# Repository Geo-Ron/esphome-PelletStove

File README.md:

# esphome-PelletStove

This repository is dedicated to documenting the maintenance, parts, communication and controls of the pellet stove my mother bought recently (september 2024).

I am going to be a parasite and feed on the work of someone else: https://github.com/jazzmonger/wood-pellet-stove-with-TYWE1S-Tuya-chip. Read his [discussions section](https://github.com/jazzmonger/wood-pellet-stove-with-TYWE1S-Tuya-chip/discussions), they are AWESOME! Many, many, many thanks in advanced.

## The story

<details>
  <summary>In short: the gas fireplace was replaced with a used pellet stove.</summary>
  
My mother (80+) and father (70+) were really happy with their gas stove.

They enjoyed the warmth and liked turning the heat up to more then 22°C, as most elderly people do.

I remember I always had a hard time staying awake in these temperatures in winter times.

But then the war in Ukrain broke loose and gas prices went up in the Netherlands. My parents were shocked by the news reports about the high gas prices and decided to stop turning on the gas fireplace to lower their monthly costs.

In basis that was a really good decision, if it were not for the fact that their 1960's house was not that nicely isolated.

Their next decision was to stop heating around 18h and heat only the living room with an electric heater up to 19°C. My mother also bought a cordless electric heating cushion for her back.

It was kind of okay for them, with some amount of complaining by my mother. She wore several layers of clothing and still was not comfortable.

I then decided to look for an alternative for their unused gas fireplace, but was limited by the fact that they absolutely did not want to invest thousands of Euros in a new fireplace. As they stated: they were too old for such an investment.

So the search was for a used pellet stove, that would fit the hole in the wall.

It took me more then a year to find one with an acceptable price. My father passed away during my search, so he was not going to benefit from it anymore.

Then I found one, the price was okay. The seller did not know of a manufacturer or model number. The gamble was on me to risk the money of someone else. 

The seller was nice and told us he had a good history with this stove. The reason for him to sell it was that it was getting too hot in his home. In my opinion that was not going to be an issue at my mothers place.

The device was demo-ed and we took it home.

</details>

## The 'new' pellet stove

<details>
<summary>
We bought a HY IN9A. Probably this is a rebranded device sold by the company 'Justfire' in the Netherlands. The original manufacturer is [HYStove](https://hystove.en.alibaba.com/)
</summary>

When Google-ing the model name, this led us to the site [http://histove.com](http://histove.com/?AirPelletStove/51.html). The manufacturing company (I assume) is HAINING HEYING HEATING TECHNOLOGY CO., LTD.

At this moment sold at [Alibaba.com](https://www.alibaba.com/product-detail/House-heating-use-modern-eco-friendly_62325821470.html)

### Site Model information

Model: **HY-IN9A**

Capacity: _9KW_

Description: 2019 newly designed European style insert wood pellet stove

| Product parameters(HY-IN9A) |                 |
|-----------------------------|-----------------|
| Heat Area                   | 100㎡            |
| Dimension(W\*H\*D)          | 807\*635\*621mm |
| Air input pipe              | 50mm            |
| Air outlet pipe             | 80mm            |
| Auto-burning Time           | 13h-27h         |
| Consumption for pellet      | 0.8-1.8kg/h     |
| Efficiency                  | 90%             |
| Hopper Capacity             | 23kg            |
| Electronic comsuotion       | 100-400W/h      |
| Rating voltage              | 230v            |

Specifications:

1. Outside: steel coating.
2. Inside: monobloc steel structure, hand welded, heat-resistant up to 1200°C.
3. Door: carbon steel, high temperature resistant, with glass-ceramic.
4. Removable ash box: it collects the ash fallen through the holes in the brazier.
5. Glass-self cleaning: designing wind to blow ash from the glass keeps the glass always cleaning.
6. LCD control panel: it is placed on the upper side of the stove, simple and easy to be used. It is possible to plan the weekly switching on and off of the stove (week-end included).
7. Thermostat: The stove can keep the room's temperature stably. The temperature can be selected by users both on the panel and remote control, showing on the display.
8. Five steps power setting: it is up to your need, which also shows on the display.
9. Remote control
10. Smoke outlet: ø 80 mm, inlet ø 50 mm
11. Electrical supply: 230V-50Hz. 115V-60HZ, 100V-50HZ

### Not entirely true

As one can read, the information provided is mostly correct. So that is a starting point.

### Image search

So I tried to image search the stove I bought and there were several options:

- It is sold as a [Justfire PS-15-5 BUILDIN](https://justfire.nl/pellethaard-9kw-standard-type-black-2500.html)
- It is a Nemaxx stove (once sold in Germany)
  - The Nemaxx P6 is **identical** to the HY 6A.
- Cleveland Ironworks stove.
  - Their model [No.215](https://www.cleveland-ironworks.com/no-215-mini-pellet-stove.html) really looks like the same HY 6A.
- But also other brands: Sole, Grace Ningbo

</details>

## First basic maintenance

<details>
<summary>
Getting spare parts is not 'cheap'
</summary>

I am by no means a pellet stove expert. Let me get this out first.

What I am is a technical person. Problem solving is my job and I really like making things simple.

So I used my ash-vacuum-cleaner and take a deeper look into it.

The stove was almost clean, with some sealings ruptured.

Then I asked the company Justfire for a maintenance quote, and their response was this:

- Incidental maintenance: €300,-
- the mainboard (MCU) would need replacement because of a fire hazard: €200,-
- the display would need to match the MCU and would also be replaced: €170,-
- the ruptured seals would probably be included in the maintenance, if not that would add another €80,-

**No way that I am going to pay €750,-** for a first maintenance and inspection. They did not ask me for any serial number, model number, date of manufacturing or anything else.

I investigated other sellers for just the sealing-replacements than Justfire, but was unable to find all the seals that I needed. So I paid €80,- for two sealings at Justfire. These I can replace myself easily.

Half an hours of vacuuming, brushing and replacing the seals and we are in business for now.

</details>

### Spare parts

I will list all the parts I buy and/or replace in [parts-list.md](./parts-list.md).

### The missing remote

<details>
<summary>Unable to find a replacement remote control
</summary>

I found out the stove should have a remote. This would be nice so my mother would not need to bend over to control the stove.

I was unable to find a replacement remote for a price less then €80,-. That is too much as far as I am concerned. No guarantees that the remote would work anyway.

Justfire also sells a WiFi module for the ginormous amount of €160,-. But for an extra €160,- they are willing to configure it for me 😄.

</details>

### And then I found the jazzmonger github repository

When I found the [Github repository of Jazzmonger](https://github.com/jazzmonger/wood-pellet-stove-with-TYWE1S-Tuya-chip) I was overwhelmed with his work and enthousiasm. Wow!

I already have an [HomeAssistant](https://www.home-assistant.io/) instance at my mothers house, to monitor gas usage and room temperatures. It would really be a nice addition to connect the stove to it.

What I would really like to accomplish is:

- Be able to remotely control the stove from HomeAssistant
  - Turn it on/off
  - change the ECO mode
  - change the P1-4 modes
  - be able to measure temperatures
  - reading the stove 'states'
  - detect and reset errors
  - monitor the pellet level
- All without any 'special' PCBs to buy
  - I mean, I have several ESP32's laying around and I am willing to assemble a PCB of some sort and order material.

But most, if not all, of the heavy lifting has been done by [Jazzmonger](https://github.com/jazzmonger) already.

What I need to do is:

- Understand what he has accomplished, how it works and how to copy/adapt/improve his work.
  - I will be returning to him as I improve. Promised.

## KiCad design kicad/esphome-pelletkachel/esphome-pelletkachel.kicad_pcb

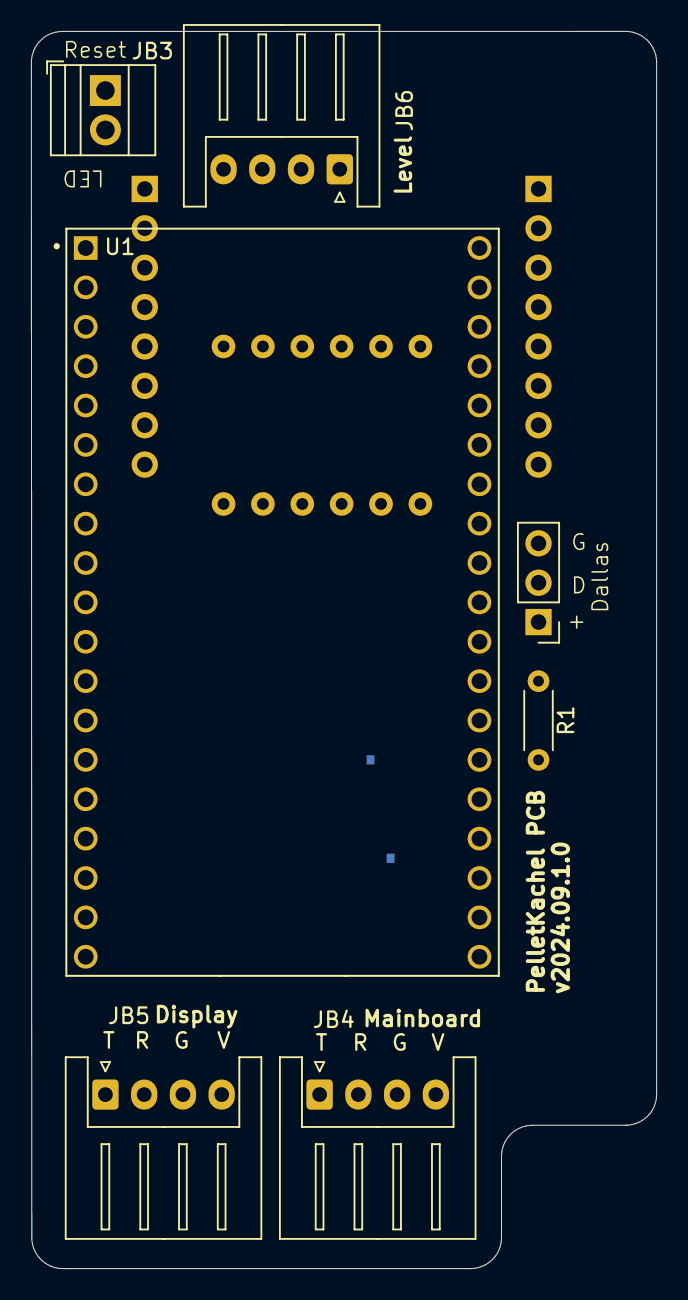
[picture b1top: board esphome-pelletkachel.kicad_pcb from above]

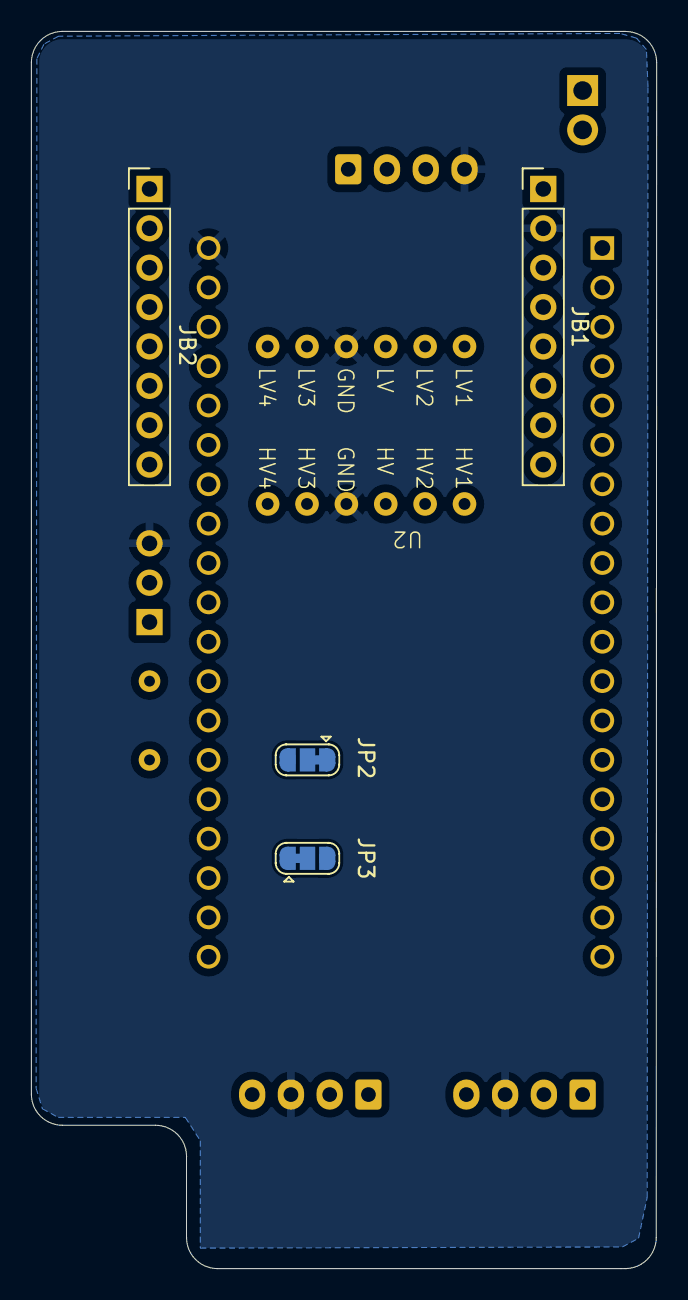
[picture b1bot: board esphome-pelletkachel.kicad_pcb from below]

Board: 2 copper layers, 40.3 x 79.8 mm, 12 parts (5 on the bottom side), 19 nets, no tracks yet.

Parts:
J6: 1-wire; PinHeader_1x03_P2.54mm_Vertical
JB1: J5 Even; PinHeader_1x08_P2.54mm_Vertical
JB2: J5 Odd; PinHeader_1x08_P2.54mm_Vertical
JB3: Thumbs; TerminalBlock_Xinya_XY308-2.54-2P_1x02_P2.54mm_Horizontal
JB4: Mainboard (DPC); JST_XH_S4B-XH-A_1x04_P2.50mm_Horizontal
JB5: Display (J1); JST_XH_S4B-XH-A_1x04_P2.50mm_Horizontal
JB6: To TOF; JST_XH_S4B-XH-A_1x04_P2.50mm_Horizontal
JP2: RX switcher; SolderJumper-3_P1.3mm_Bridged12_RoundedPad1.0x1.5mm
JP3: TX switcher; SolderJumper-3_P1.3mm_Bridged12_RoundedPad1.0x1.5mm
R1: 1k; R_Axial_DIN0204_L3.6mm_D1.6mm_P5.08mm_Horizontal
U1: ESP32-DEVKITC-32U; MODULE_ESP32-DEVKITC-32U
U2: 757; TT-4chLLC-SKU000275

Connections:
+3.3V: J6.1, JB6.1, U1.1 (3V3), U2.9 (LV)
+5V: JB1.1, JB4.4 (V), JB5.4 (V), U1.19 (EXT_5V), U2.3 (HV)
/LED: JB3.2, U1.12 (IO14)
/MCU UART RX Read: U1.31 (IO19), U2.8 (LV2)
/MCU UART TX Read: U1.27 (IO16), U2.7 (LV1)
/MCURX: JB4.2 (R), JB5.2 (R), U2.2 (HV2)
/MCUTX: JB4.1 (T), JB5.1 (T), U2.1 (HV1)
/RX to Display: U1.34 (RXD0), U2.11 (LV3)
/RX to Display (HV): JB1.5, JP2.2 (C)
/Reset: JB3.1, U1.10 (IO26)
/SCL: JB6.3, U1.36 (IO22)
/SDA: JB6.2, U1.33 (IO21)
/TX to Display: U1.35 (TXD0), U2.12 (LV4)
/TX to Display (HV): JB1.6, JP3.2 (C)
GND: J6.3, JB1.2, JB4.3 (G), JB5.3 (G), JB6.4, U1.38 (GND3), U2.4 (HV_GND), U2.10 (LV_GND)
unnamed: J6.2, R1.2
unnamed: JP2.1 (A), JP3.3 (B), U2.5 (HV3)
unnamed: JP2.3 (B), JP3.1 (A), U2.6 (HV4)
unnamed: R1.1, U1.37 (IO23)

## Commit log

2024-09-20 first commits
2024-09-20 added some pictures
2024-09-20 indentation
2024-09-20 dikte
2024-09-20 added documents
2024-09-20 rename
2024-09-20 done for now
2024-09-20 text changed
2024-09-20 added error codes
2024-09-20 top secret
2024-09-20 extra info
2024-09-21 additions
2024-09-21 added pellet level
2024-09-21 tekst
2024-09-21 indetation
2024-09-21 changed text
2024-09-22 stolen vendor notes
2024-09-22 check
2024-09-22 added kicad files
2024-09-22 remove backups
2024-09-22 first gitignore
2024-09-22 corrected gitignore
2024-09-22 changed drawing
2024-09-22 corrections
2024-09-22 changed gitignore
2024-09-27 some edits
2024-09-27 completed schematic so far
2024-09-27 improvements
2024-09-27 first pcb tests
2024-09-28 changed schematic
2024-09-28 this is hard
2024-09-28 annotations
2024-09-28 latest changes
2024-09-29 gefreubel
2024-09-29 added tx rx switching method
2024-09-29 weer even uitgespeeld
2024-09-29 zooo
2024-09-29 ignore the output files
2024-09-30 autorouted
2024-09-30 ewsonw
2024-10-03 gedoe
2024-10-03 wat gefreubelt
2024-10-04 beetje geschoven
2024-10-17 changed recommendations
2024-10-20 added settings
2024-10-20 stove settings added
2024-10-20 added stove settings
2024-10-20 rename again
2024-10-21 additions to settings
2024-10-21 added hex
2024-10-22 wijzigingen
2024-10-22 nog een toevoeging
2024-10-22 instructiegids
2024-10-22 settings
2024-10-22 pictures added
2024-10-22 added model
2024-10-25 toevoegingen
2024-10-25 new mainboard
2024-10-25 text
2024-10-27 added new settings after hardware swap
2024-10-27 newline
2024-10-27 text changes
2024-10-27 added pcitures
2024-10-27 added toc
2024-10-27 toc added
2024-10-27 wiring added
2024-10-27 pdf added
2024-10-27 added text
2024-10-28 removed opinion
2024-10-28 more settings!!!
2024-10-28 ntc test
2024-10-28 only temp
2024-10-28 better output
2024-10-28 changed
2024-10-29 added new settings
2024-10-29 added brands
2024-10-30 moved code
